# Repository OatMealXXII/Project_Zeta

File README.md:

# IoT Carrier Board for Raspberry Pi Pico 2 / 2W (Project Zeta) - Rev 1.1

A rugged, modular IoT carrier board designed for Raspberry Pi Pico 2 and Pico 2W microcontrollers deployed in harsh outdoor, telemetry, and edge-computing environments. This board integrates primary surge protection, reverse-polarity defense, isolated grounding, and sensor interface expansion.

---

## Architecture & Design Highlights

- **Modular Carrier Architecture:** Separates power handling, field protection, and physical wiring from the core logic board, enabling hot-swap servicing and low maintenance overhead.
- **Hardware-First Resilience (KISS Principle):** Built entirely with robust discrete semiconductors and passive protection networks, eliminating fragile active supervisory ICs and maintaining zero quiescent current drain.
- **Sub-Layer High-Energy Routing:** High-current surge paths and gas discharge loops are isolated on the bottom layer to eliminate transient EMI coupling into sensitive microcontroller logic.
- **Dual-Domain Ground Separation:** Features a dedicated `*Earth ⏚` path isolated from logic/signal GND, specifically routed to safely divert atmospheric lightning surges and external ESD directly into structural grounding.

---

## Power & Surge Protection Subsystem

```

[External Surge / Lightning ESD]
│
▼
[GDT (GD1)] ────────────────────────► *Earth ⏚ (Chassis / Field Ground)
│
[DC Input / 1S Li-ion Battery]                  │ (Isolated Domain)
│                                   ▼
▼                              [Earth Rod]
[SS14 Schottky (D1)] ───► (Reverse-Polarity Protection)
│
├───────────────► [TVS Diode (D2)] ──► Signal GND (Overvoltage Clamping)
│
├───────────────► [100µF Bulk Cap]  ──► Signal GND (Inrush & Transient Reservoir)
├───────────────► [100nF Ceramic]   ──► Signal GND (High-Frequency Decoupling)
│
▼
[Regulated VCC Bus / 3V3_EXT Rail to Pico & Sensor Interfaces]

```

### Component Specifications & Engineering Justification

| Designator | Component | Specification / Package | Engineering Function |
| :--- | :--- | :--- | :--- |
| **`GD1`** | **Gas Discharge Tube (GDT)** | 2-Electrode Axial (Spark-over: ~90V–230V) | **Primary surge barrier.** Shunts high-energy transient spikes (kA surge capacity) directly to earth ground without burning the PCB traces. |
| **`D1`, `D3`** | **Schottky Barrier Diode** | SS14 (1A / 40V, SMA / DO-214AC) | Blocks reverse-polarity voltage connection with ultra-low forward voltage drop ($V_F \approx 0.35\text{V}$) on input buses. |
| **`D2`, `D4`** | **TVS / Clamping Diode** | SMAJ5.0A (SMA / DO-214AC) | Suppresses residual fast transients and clamps overvoltage to safe logic thresholds within nanosecond response times. |
| **`C1`, `C3`** | **Electrolytic Capacitor** | 100µF (Radial, Low ESR) | Absorbs input voltage dips and supplies peak burst current during Wi-Fi / LoRa transmission cycles. |
| **`C2`, `C4`** | **Ceramic Capacitor** | 100nF (Radial / Multilayer) | Suppresses high-frequency switching noise adjacent to power distribution headers. |
| **`J1`, `J2`** | **Female Pin Headers** | 1x20 Pin 2.54mm Pitch | Socket interface for Raspberry Pi Pico 2 / Pico 2W. |

---

## Power Subsystem & Battery Management

- **Supported Input Topology:** 1S Li-ion / LiFePO4 battery pack (1S1P, 1S2P, 1S4P) or 5V DC step-down source.
- **Operating Input Range:** **1.8V to 5.5V DC** (Strictly single-cell architecture; **do NOT connect 2S, 3S, or 4S packs** directly without external regulation).
- **External BMS Coordination:** Designed to interface with an external 1S Lithium BMS module handling cell balancing, overcharge (4.2V cut-off), and deep over-discharge protection.
- **Dedicated Sensor Power Bus (`3V3_EXT`):** Independent power tap engineered to prevent high-draw peripheral sensors from loading or resetting the internal Pico voltage regulator.

---

## Commissioning & Verification Guide (Smoke Test)

### Step 1: Cold Test & Continuity Inspection (Unpowered)
1. Verify silkscreen polarity symbols (`+`, `-`, and `*Earth ⏚`) across all terminal blocks.
2. Check resistance with a digital multimeter between `VCC` and `GND` across all power rails.
   - *Pass Criteria:* High impedance / open circuit ($>1\text{ M}\Omega$).
3. Verify that `*Earth ⏚` is completely isolated from system `GND` on the multimeter.
4. Test diodes `D1`–`D4` in Diode Check mode to ensure correct cathode/anode orientation.

### Step 2: First Power-Up (Current-Limited Test)
1. Set a bench power supply to **3.8V DC** with the current limit restricted to **50mA**.
2. Connect leads to the power terminal blocks (without the Raspberry Pi Pico mounted).
3. Measure voltage rails at pin sockets: verify clean DC voltage across `VCC`, `3V3_EXT`, and ground buses.
   - *Pass Criteria:* Quiescent current remains $<1\text{mA}$; no thermal dissipation across protection diodes.

### Step 3: Full-Load Runtime Validation
1. Power down and securely seat the Raspberry Pi Pico 2 / 2W into headers `J1` and `J2`.
2. Increase the power supply current limit to **500mA**.
3. Flash edge telemetry firmware and verify Wi-Fi/LoRa transmission stability under active load.

---

## Roadmap

- [x] **Rev 1.0 (Prototype):** Initial 2-layer modular layout; verified discrete protection logic and basic terminal block layout.
- [x] **Rev 1.1 (Current Production):**
  - Added dedicated Primary Surge Stage via Gas Discharge Tube (**GD1**) paired with isolated **`*Earth ⏚`** terminal block.
  - Symmetrical dual-rail topology with auxiliary high-current sensor power (**`3V3_EXT`**).
  - Optimized footprint clearances (eliminated SMD diode soldering crowding from Rev 1.0).
  - Strict 45° trace angle routing across both layers to eliminate acid traps and maintain signal integrity.
- [ ] **Rev 2.0 (Planned):** 4-layer impedance-controlled stackup with dedicated inner ground and power planes (L2/L3), integrated MIFA antenna, and expanded energy-harvesting interfaces.

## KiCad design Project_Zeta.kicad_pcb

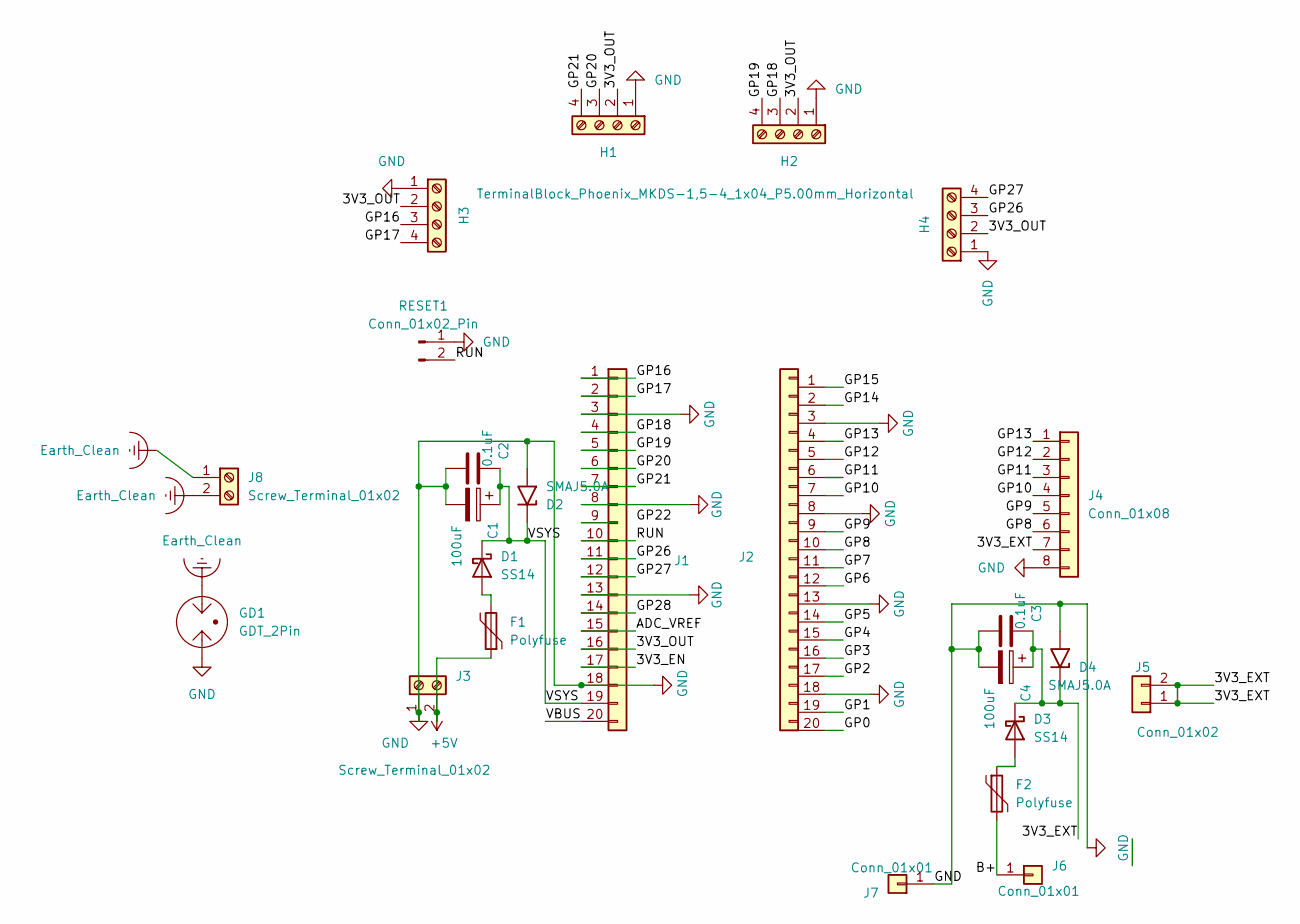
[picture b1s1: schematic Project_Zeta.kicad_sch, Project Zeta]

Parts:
C1, C4: 100uF; CP_Radial_D6.3mm_P2.50mm
C2, C3: 0.1uF; C_Disc_D5.0mm_W2.5mm_P2.50mm
D1, D3: SS14; D_SMA
D2, D4: SMAJ5.0A; D_SMA
F1, F2: Polyfuse; Fuse_Bourns_MF-RHT050
GD1: GDT_2Pin; R_Axial_DIN0411_L9.9mm_D3.6mm_P15.24mm_Horizontal
H1, H2, H3: TerminalBlock_Phoenix_MKDS-1,5-4_1x04_P5.00mm_Hor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; TerminalBlock_Phoenix_MKDS-1,5-4_1x04_P5.00mm_Horizontal
H4: TerminalBlock_Phoenix_MKDS-1,5-4_1x04_P5.08mm_Hor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; TerminalBlock_Phoenix_MKDS-1,5-4_1x04_P5.00mm_Horizontal
J1, J2: Conn_01x20; PinSocket_1x20_P2.54mm_Vertical
J3, J8: Screw_Terminal_01x02; TerminalBlock_Phoenix_MKDS-1,5-2_1x02_P5.00mm_Horizontal
J4: Conn_01x08; PinHeader_1x08_P2.54mm_Horizontal
J5: Conn_01x02; PinHeader_1x02_P2.54mm_Horizontal
J6, J7: Conn_01x01; SolderWire-0.25sqmm_1x01_D0.65mm_OD2mm
RESET1: Conn_01x02_Pin; PinHeader_1x02_P2.54mm_Vertical

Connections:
+5V: F1.1, J3.2
/3V3_EN: J1.17 (3V3_EN)
/3V3_EXT: C3.1, C4.1, D3.1 (K), D4.1 (A1), J4.7, J5.1, J5.2
/3V3_OUT: H1.2, H2.2, H3.2, H4.2, J1.16 (3V3_OUT)
/ADC_VREF: J1.15 (ADC_VREF)
/B+: F2.2, J6.1 (Pin_1_1)
/GP0: J2.20
/GP1: J2.19
/GP2: J2.17
/GP3: J2.16
/GP4: J2.15
/GP5: J2.14
/GP6: J2.12
/GP7: J2.11
/GP8: J2.10, J4.6
/GP9: J2.9, J4.5
/GP10: J2.7, J4.4
/GP11: J2.6, J4.3
/GP12: J2.5, J4.2
/GP13: J2.4, J4.1
/GP14: J2.2
/GP15: J2.1
/GP16: H3.3, J1.1 (GP16)
/GP17: H3.4, J1.2 (GP17)
/GP18: H2.3, J1.4 (GP18)
/GP19: H2.4, J1.5 (GP19)
/GP20: H1.3, J1.6 (GP20)
/GP21: H1.4, J1.7 (GP21)
/GP26: H4.3, J1.11 (GP26)
/GP27: H4.4, J1.12 (GP27)
/GP28: J1.14 (GP28)
/RUN: J1.10 (RUN), RESET1.2
/VBUS: J1.20 (VBUS)
/VSYS: C1.1, C2.1, D1.1 (K), D2.1 (A1), J1.19 (VSYS)
Earth_Clean: GD1.2, J8.1, J8.2
GND: C1.2, C2.2, C3.2, C4.2, D2.2 (A2), D4.2 (A2), GD1.1, H1.1, H2.1, H3.1, H4.1, J1.3 (GND), J1.8 (GND), J1.13 (GND), J1.18 (GND), J2.3, J2.8, J2.13, J2.18, J3.1, J4.8, J7.1 (Pin_1_1), RESET1.1
unnamed: D1.2 (A), F1.2
unnamed: D3.2 (A), F2.1

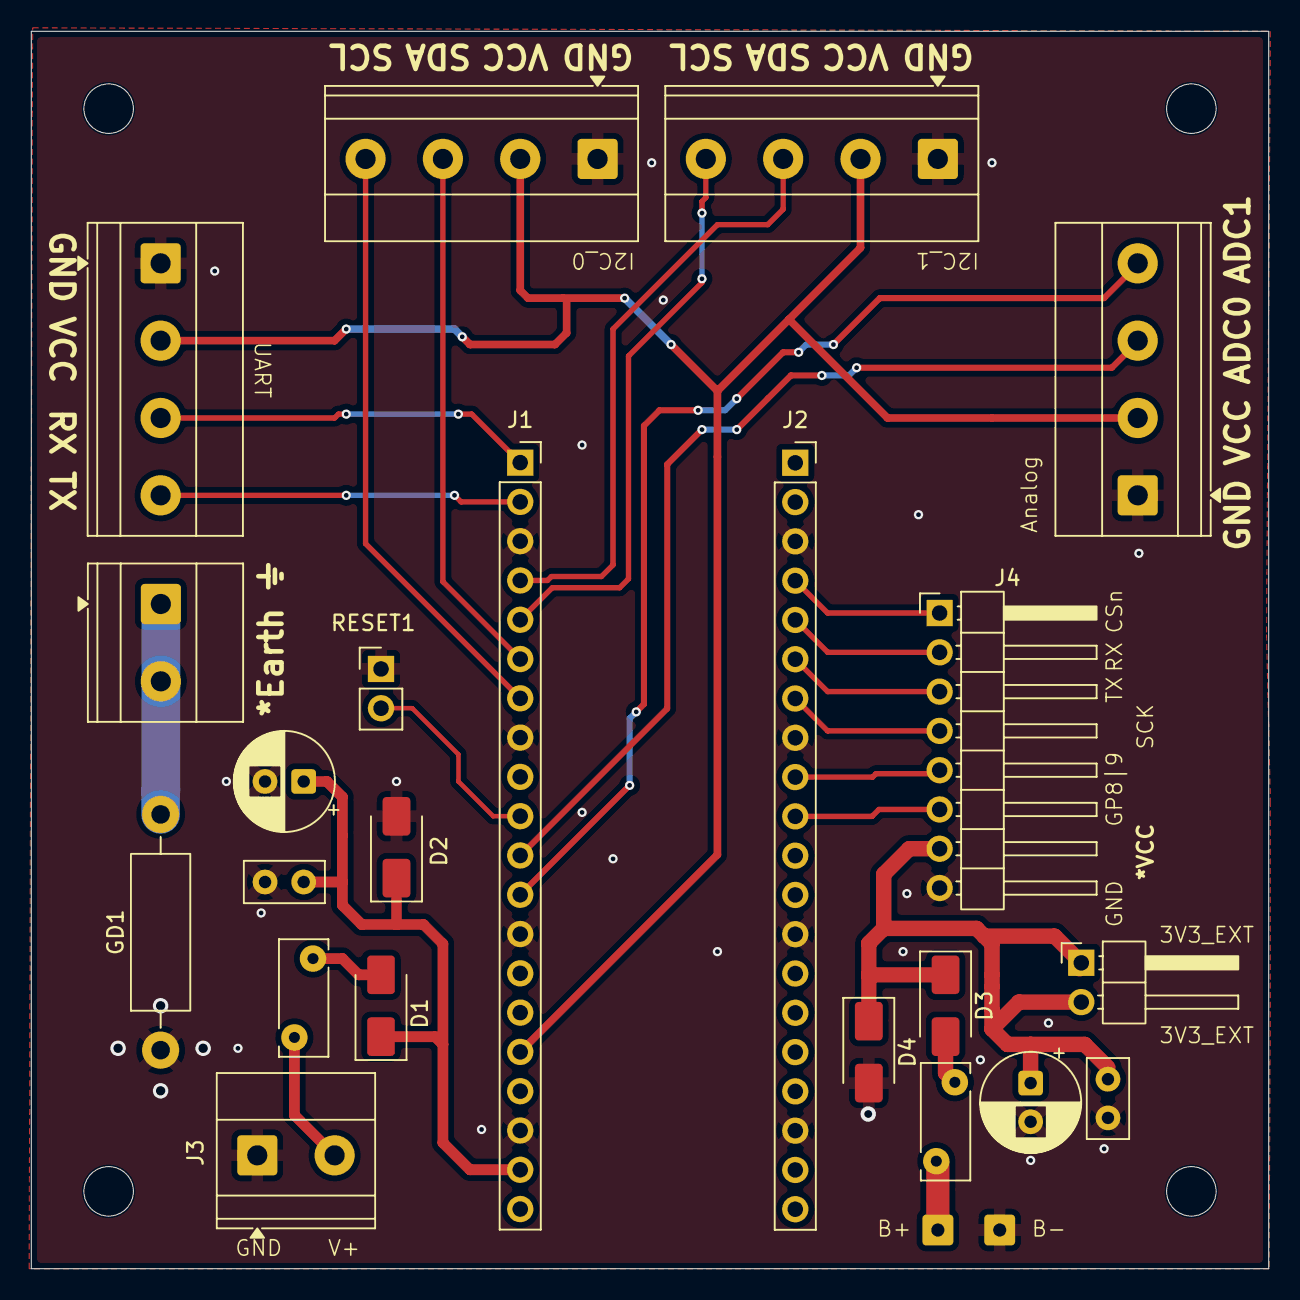
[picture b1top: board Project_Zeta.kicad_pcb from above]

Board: 2 copper layers, 80.0 x 80.0 mm, 24 parts (0 on the bottom side), 24 nets.
